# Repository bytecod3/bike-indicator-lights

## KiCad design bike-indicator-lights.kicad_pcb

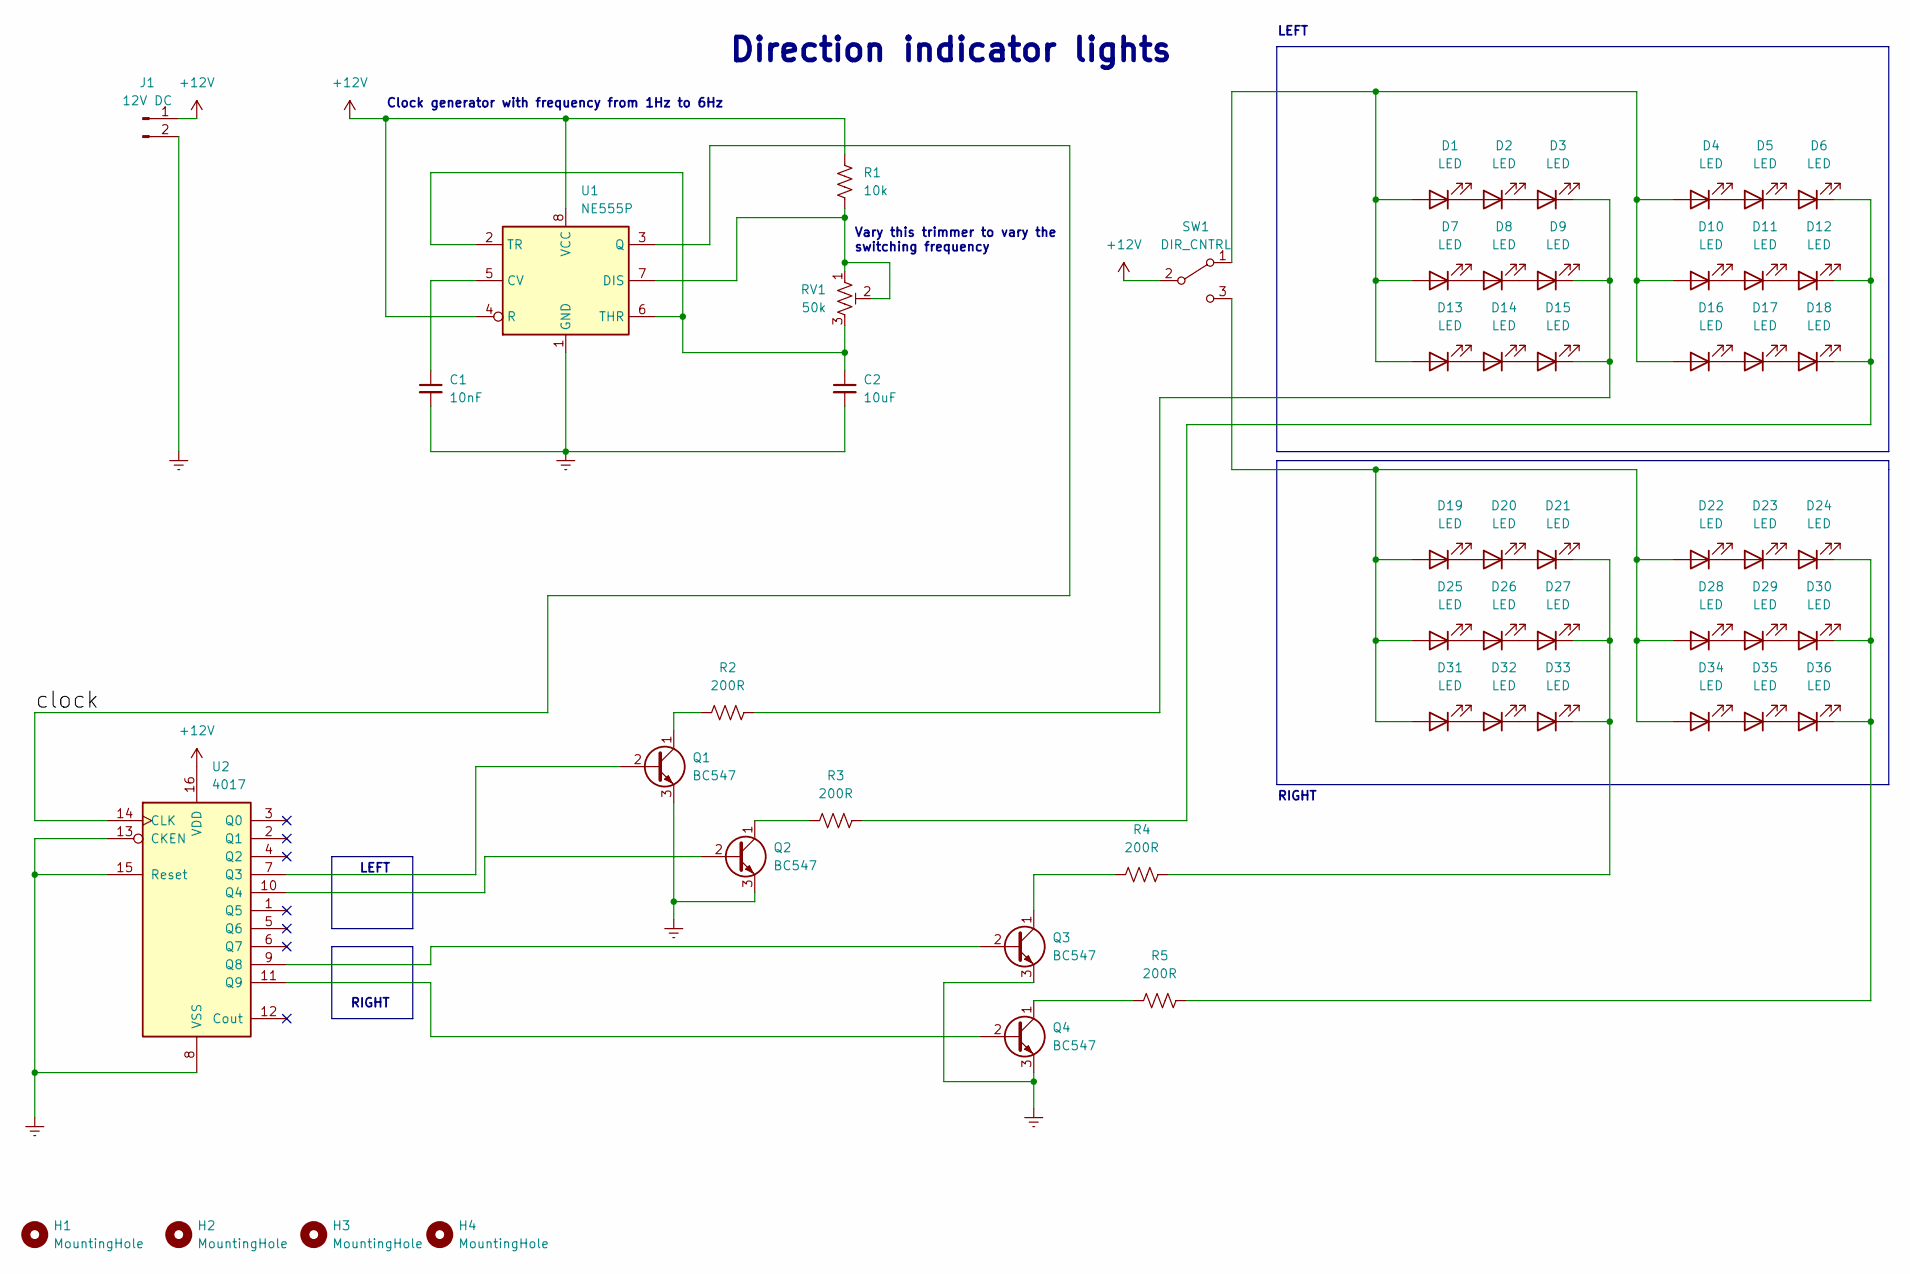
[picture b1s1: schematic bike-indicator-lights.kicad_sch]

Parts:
C1: 10nF; C_Rect_L11.5mm_W3.2mm_P10.00mm_MKT
C2: 10uF; CP_Radial_D8.0mm_P3.80mm
D1, D2, D3, D4, D5, D6, D7, D8, D9, D10, D11, D12, D13, D14, D15, D16, D17, D18, D19, D20, D21, D22, D23, D24, D25, D26, D27, D28, D29, D30, D31, D32, D33, D34, D35, D36: LED; LED_D5.0mm
H1, H2, H3, H4: MountingHole; MountingHole_2.2mm_M2_DIN965_Pad_TopOnly
J1: 12V DC; JST_EH_B2B-EH-A_1x02_P2.50mm_Vertical
Q1, Q2, Q3, Q4: BC547; TO-92_Inline
R1: 10k; R_Axial_DIN0207_L6.3mm_D2.5mm_P10.16mm_Horizontal
R2, R3, R4, R5: 200R; R_Axial_DIN0207_L6.3mm_D2.5mm_P10.16mm_Horizontal
RV1: 50k; Potentiometer_ACP_CA14V-15_Vertical_Hole
SW1: DIR_CNTRL; SW_E-Switch_EG2219_DPDT_Angled
U1: NE555P; DIP-8_W7.62mm
U2: 4017; DIP-16_W7.62mm_LongPads

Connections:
+12V: J1.1, R1.1, SW1.2 (B), U1.4 (R), U1.8 (VCC), U2.16 (VDD)
/clock: U1.3 (Q), U2.14 (CLK)
Earth: C1.2, C2.2, J1.2, Q1.3 (E), Q2.3 (E), Q3.3 (E), Q4.3 (E), U1.1 (GND), U2.8 (VSS), U2.13 (CKEN), U2.15 (Reset)
unnamed: C1.1, U1.5 (CV)
unnamed: C2.1, RV1.3, U1.2 (TR), U1.6 (THR)
unnamed: D1.1 (K), D2.2 (A)
unnamed: D1.2 (A), D4.2 (A), D7.2 (A), D10.2 (A), D13.2 (A), D16.2 (A), SW1.1 (A)
unnamed: D2.1 (K), D3.2 (A)
unnamed: D4.1 (K), D5.2 (A)
unnamed: D5.1 (K), D6.2 (A)
unnamed: D7.1 (K), D8.2 (A)
unnamed: D8.1 (K), D9.2 (A)
unnamed: D10.1 (K), D11.2 (A)
unnamed: D11.1 (K), D12.2 (A)
unnamed: D6.1 (K), D12.1 (K), D18.1 (K), R3.2
unnamed: D13.1 (K), D14.2 (A)
unnamed: D14.1 (K), D15.2 (A)
unnamed: D3.1 (K), D9.1 (K), D15.1 (K), R2.2
unnamed: D16.1 (K), D17.2 (A)
unnamed: D17.1 (K), D18.2 (A)
unnamed: D19.1 (K), D20.2 (A)
unnamed: D19.2 (A), D22.2 (A), D25.2 (A), D28.2 (A), D31.2 (A), D34.2 (A), SW1.3 (C)
unnamed: D20.1 (K), D21.2 (A)
unnamed: D21.1 (K), D27.1 (K), D33.1 (K), R4.2
unnamed: D22.1 (K), D23.2 (A)
unnamed: D23.1 (K), D24.2 (A)
unnamed: D24.1 (K), D30.1 (K), D36.1 (K), R5.2
unnamed: D25.1 (K), D26.2 (A)
unnamed: D26.1 (K), D27.2 (A)
unnamed: D28.1 (K), D29.2 (A)
unnamed: D29.1 (K), D30.2 (A)
unnamed: D31.1 (K), D32.2 (A)
unnamed: D32.1 (K), D33.2 (A)
unnamed: D34.1 (K), D35.2 (A)
unnamed: D35.1 (K), D36.2 (A)
unnamed: Q2.1 (C), R3.1
unnamed: Q2.2 (B), U2.10 (Q4)
unnamed: Q4.1 (C), R5.1
unnamed: Q4.2 (B), U2.11 (Q9)
unnamed: R1.2, RV1.1, RV1.2, U1.7 (DIS)
unnamed: Q1.1 (C), R2.1
unnamed: Q3.1 (C), R4.1
unnamed: Q1.2 (B), U2.7 (Q3)
unnamed: Q3.2 (B), U2.9 (Q8)

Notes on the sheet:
Direction indicator lights
LEFT
Clock generator with frequency from 1Hz to 6Hz
Vary this trimmer to vary the switching frequency
RIGHT

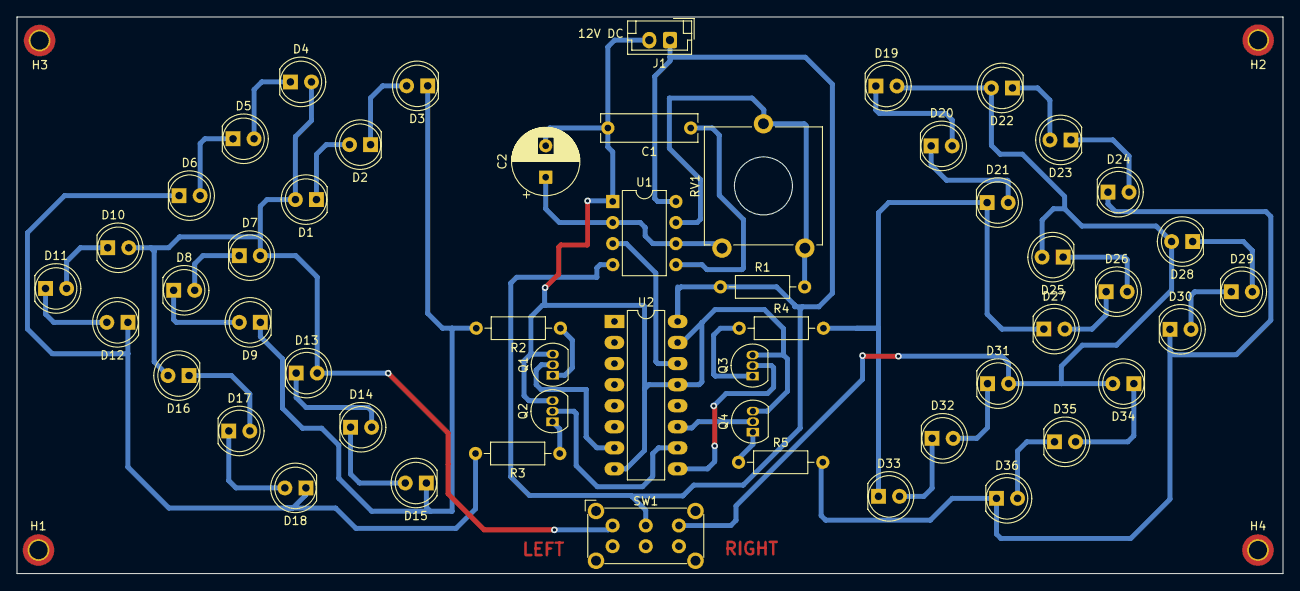
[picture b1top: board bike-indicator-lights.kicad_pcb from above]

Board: 2 copper layers, 152.7 x 67.1 mm, 56 parts (0 on the bottom side), 44 nets.

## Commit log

2023-10-16 added test-code
